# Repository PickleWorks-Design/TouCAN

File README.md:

# TouCAN

Personal Project To integrate 2 Can Adapters in 1 board with Deutch DT 3pin connectors and an onboard usb HUB

USB to Can Adapter

This Project is Based on the CANAble USB to Canbus adapter project https://github.com/makerbase-mks/CANable-MKS/tree/main/Hardware/MKS%20CANable%20V2.0

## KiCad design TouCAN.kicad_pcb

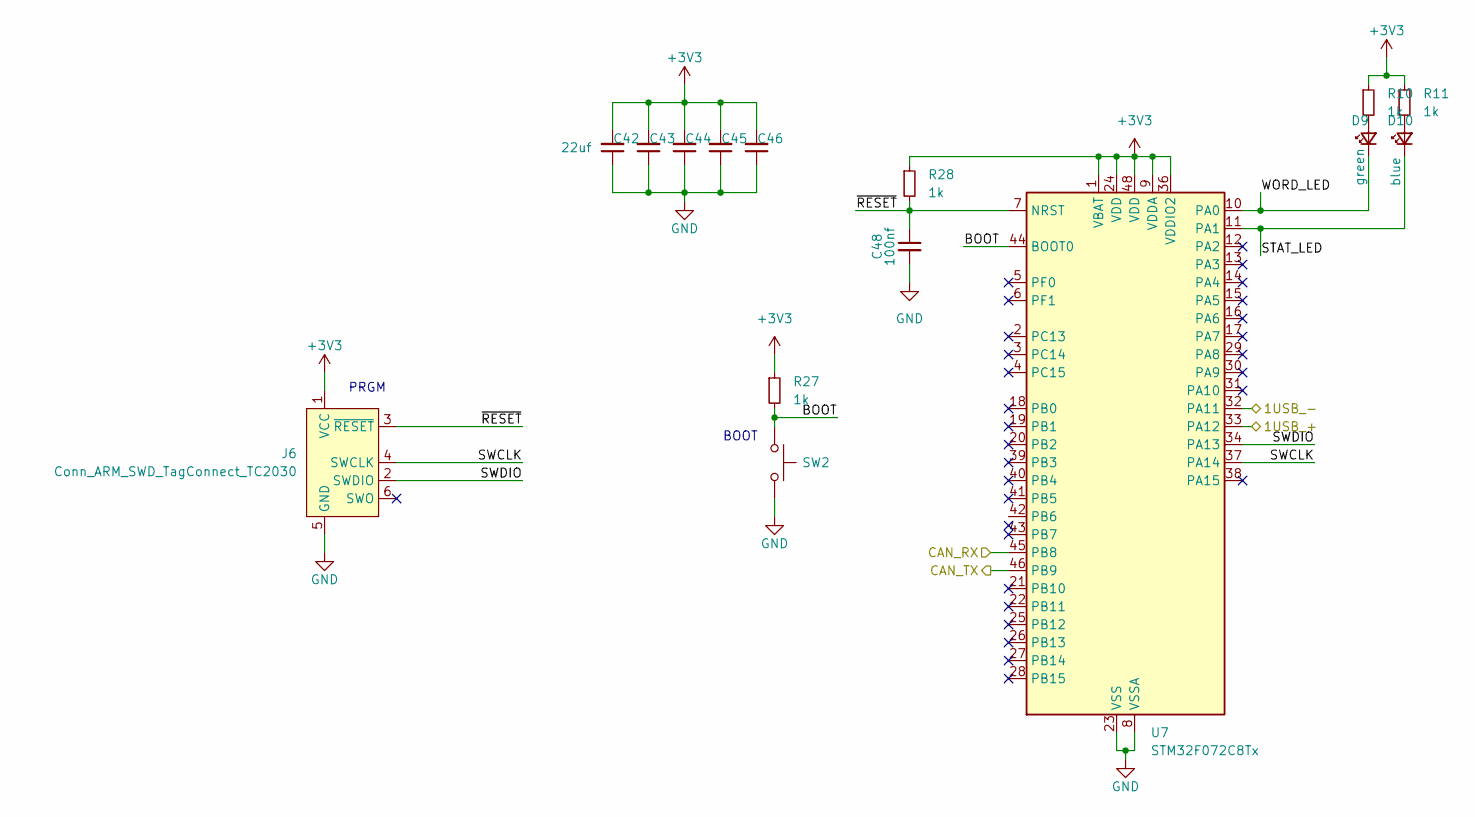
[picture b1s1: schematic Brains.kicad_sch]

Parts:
C42, C43, C44, C45, C46: 22uf; C_0603_1608Metric; LCSC C59461
C48: 100nf; C_0603_1608Metric; LCSC C14663
D9: green; LED_0603_1608Metric; LCSC C72043
D10: blue; LED_0603_1608Metric; LCSC C72041
J6: Conn_ARM_SWD_TagConnect_TC2030; Tag-Connect_TC2030-IDC-FP_2x03_P1.27mm_Vertical
R10, R11, R27, R28: 1k; R_0603_1608Metric; LCSC C21190
SW2: smol_button; LCSC C720477
U7: STM32F072C8Tx; LQFP-48_7x7mm_P0.5mm; LCSC C80488

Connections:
+3V3: C42.2, C43.2, C44.2, C45.2, C46.2, J6.1 (VCC), R10.1, R11.1, R27.1, R28.1, U7.1 (VBAT), U7.9 (VDDA), U7.24 (VDD), U7.36 (VDDIO2), U7.48 (VDD); also elsewhere on the board
/1USB_+: U7.33 (PA12); also elsewhere on the board
/1USB_-: U7.32 (PA11); also elsewhere on the board
/Brains/BOOT: R27.2, SW2.1, U7.44 (BOOT0)
/Brains/CAN_RX: U7.45 (PB8); also elsewhere on the board
/Brains/CAN_TX: U7.46 (PB9); also elsewhere on the board
/Brains/STAT_LED: D10.1 (K), U7.11 (PA1)
/Brains/SWCLK: J6.4 (SWCLK), U7.37 (PA14)
/Brains/SWDIO: J6.2 (SWDIO), U7.34 (PA13)
/Brains/WORD_LED: D9.1 (K), U7.10 (PA0)
/Brains/~RESET: C48.1, J6.3 (~RESET), R28.2, U7.7 (NRST)
GND: C42.1, C43.1, C44.1, C45.1, C46.1, C48.2, J6.5 (GND), SW2.2, U7.8 (VSSA), U7.23 (VSS), U7.35 (VSS), U7.47 (VSS); also elsewhere on the board
unnamed: D9.2 (A), R10.2
unnamed: D10.2 (A), R11.2

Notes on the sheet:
BOOT
PRGM

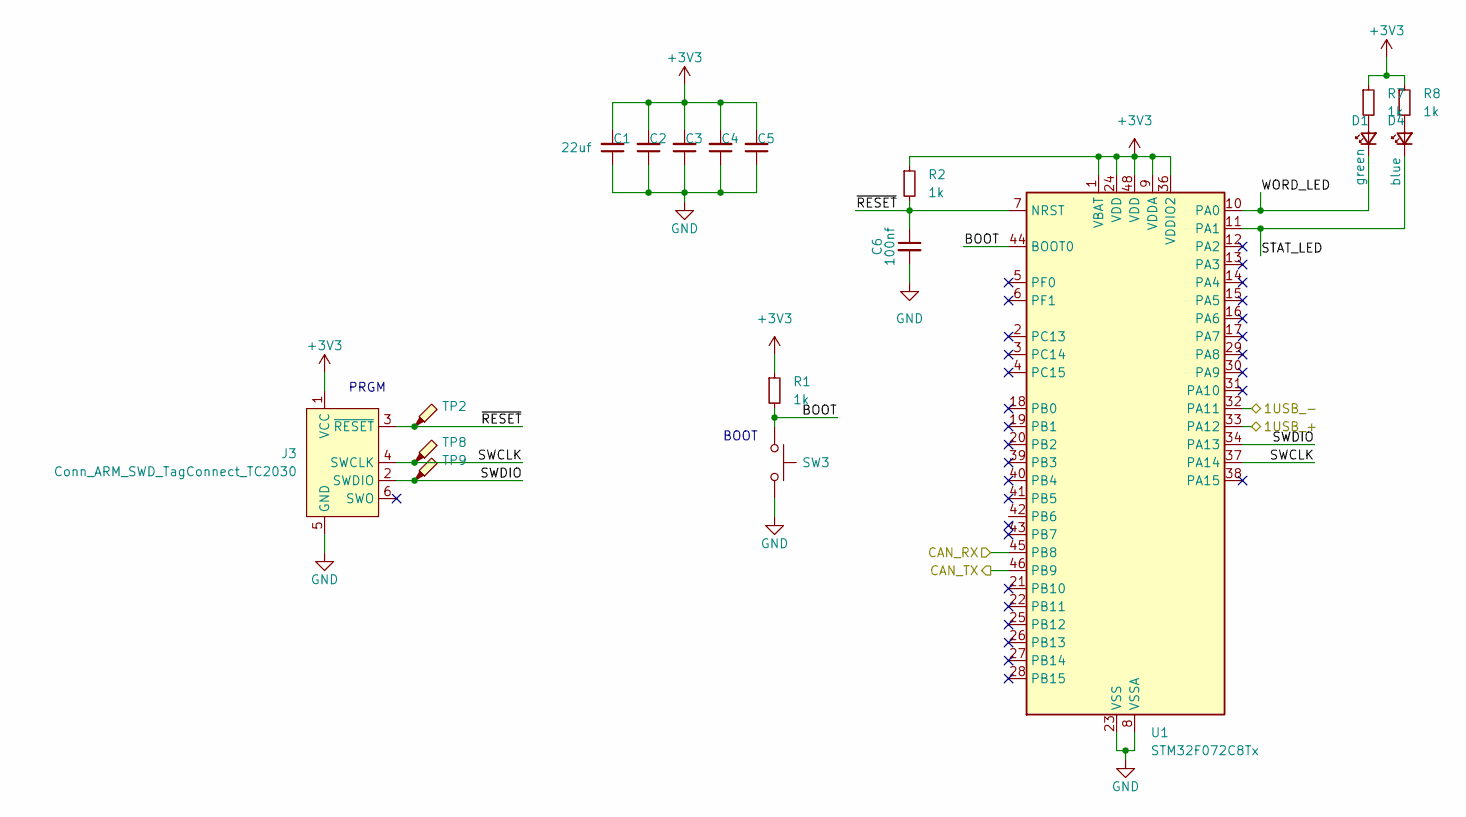
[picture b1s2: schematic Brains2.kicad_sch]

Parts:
C1, C2, C3, C4, C5: 22uf; C_0603_1608Metric; LCSC C59461
C6: 100nf; C_0603_1608Metric; LCSC C14663
D1: green; LED_0603_1608Metric; LCSC C72043
D4: blue; LED_0603_1608Metric; LCSC C72041
J3: Conn_ARM_SWD_TagConnect_TC2030; Tag-Connect_TC2030-IDC-FP_2x03_P1.27mm_Vertical
R1, R2, R7, R8: 1k; R_0603_1608Metric; LCSC C21190
SW3: smol_button; LCSC C720477
TP2, TP8, TP9: TestPoint_Probe
U1: STM32F072C8Tx; LQFP-48_7x7mm_P0.5mm; LCSC C80488

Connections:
+3V3: C1.2, C2.2, C3.2, C4.2, C5.2, J3.1 (VCC), R1.1, R2.1, R7.1, R8.1, U1.1 (VBAT), U1.9 (VDDA), U1.24 (VDD), U1.36 (VDDIO2), U1.48 (VDD); also elsewhere on the board
/2USB_+: U1.33 (PA12); also elsewhere on the board
/2USB_-: U1.32 (PA11); also elsewhere on the board
/Brains2/BOOT: R1.2, SW3.1, U1.44 (BOOT0)
/Brains2/CAN_RX: U1.45 (PB8); also elsewhere on the board
/Brains2/CAN_TX: U1.46 (PB9); also elsewhere on the board
/Brains2/STAT_LED: D4.1 (K), U1.11 (PA1)
/Brains2/SWCLK: J3.4 (SWCLK), TP8.1, U1.37 (PA14)
/Brains2/SWDIO: J3.2 (SWDIO), TP9.1, U1.34 (PA13)
/Brains2/WORD_LED: D1.1 (K), U1.10 (PA0)
/Brains2/~RESET: C6.1, J3.3 (~RESET), R2.2, TP2.1, U1.7 (NRST)
GND: C1.1, C2.1, C3.1, C4.1, C5.1, C6.2, J3.5 (GND), SW3.2, U1.8 (VSSA), U1.23 (VSS), U1.35 (VSS), U1.47 (VSS); also elsewhere on the board
unnamed: D1.2 (A), R7.2
unnamed: D4.2 (A), R8.2

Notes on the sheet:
BOOT
PRGM

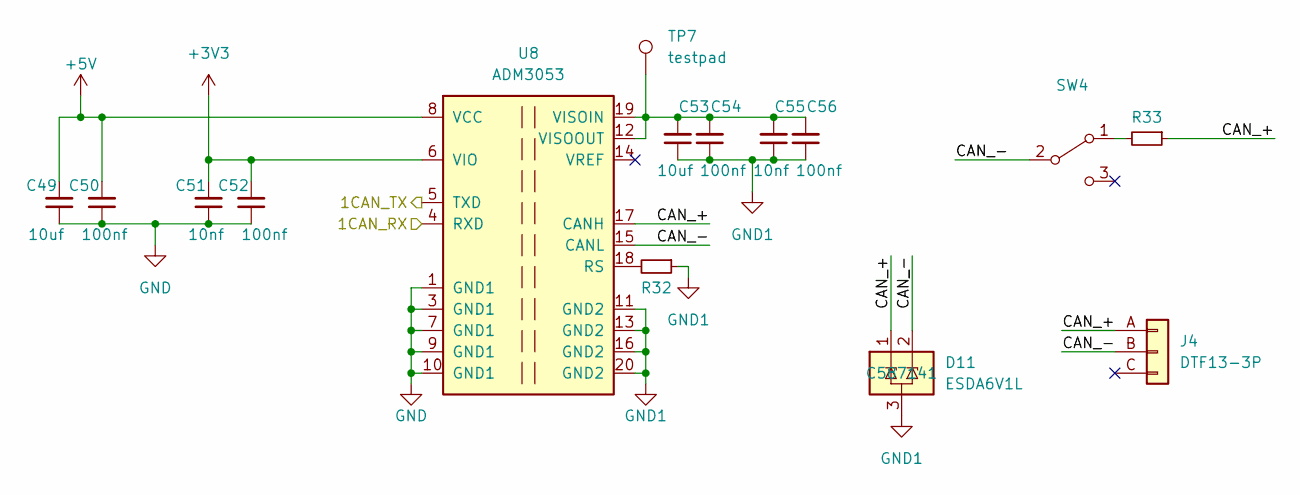
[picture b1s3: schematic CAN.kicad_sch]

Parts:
C49, C53: 10uf; C_0603_1608Metric; LCSC C96446
C50, C52, C54, C56: 100nf; C_0603_1608Metric; LCSC C14663
C51, C55: 10nf; C_0603_1608Metric; LCSC C57112
D11: ESDA6V1L; SOT-23-3; LCSC C587141
J4: DTF13-3P
R32: 10r; R_0603_1608Metric; LCSC C22859
R33: 120r; R_0603_1608Metric; LCSC C22787
SW4: MS-22C01-G010_pickle; LCSC C2837066
TP7: testpad; TestPoint_Pad_D1.0mm
U8: ADM3053; SOIC-20W_7.5x12.8mm_P1.27mm; LCSC C117821

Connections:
+3V3: C51.2, C52.2, U8.6 (VIO); also elsewhere on the board
+5V: C49.2, C50.2, U8.8 (VCC); also elsewhere on the board
/Brains/CAN_RX: U8.5 (TXD); also elsewhere on the board
/Brains/CAN_TX: U8.4 (RXD); also elsewhere on the board
/CAN/CAN_+: D11.1 (IO1), J4.A (Pin_1), R33.1, U8.17 (CANH)
/CAN/CAN_-: D11.2 (IO2), J4.B (Pin_2), SW4.2 (B), U8.15 (CANL)
GND: C49.1, C50.1, C51.1, C52.1, U8.1 (GND1), U8.3 (GND1), U8.7 (GND1), U8.9 (GND1), U8.10 (GND1); also elsewhere on the board
GND1: C53.1, C54.1, C55.1, C56.1, D11.3 (GND), R32.1, U8.11 (GND2), U8.13 (GND2), U8.16 (GND2), U8.20 (GND2)
unnamed: R33.2, SW4.1 (A)
unnamed: R32.2, U8.18 (RS)
unnamed: C53.2, C54.2, C55.2, C56.2, TP7.1, U8.12 (VISOOUT), U8.19 (VISOIN)

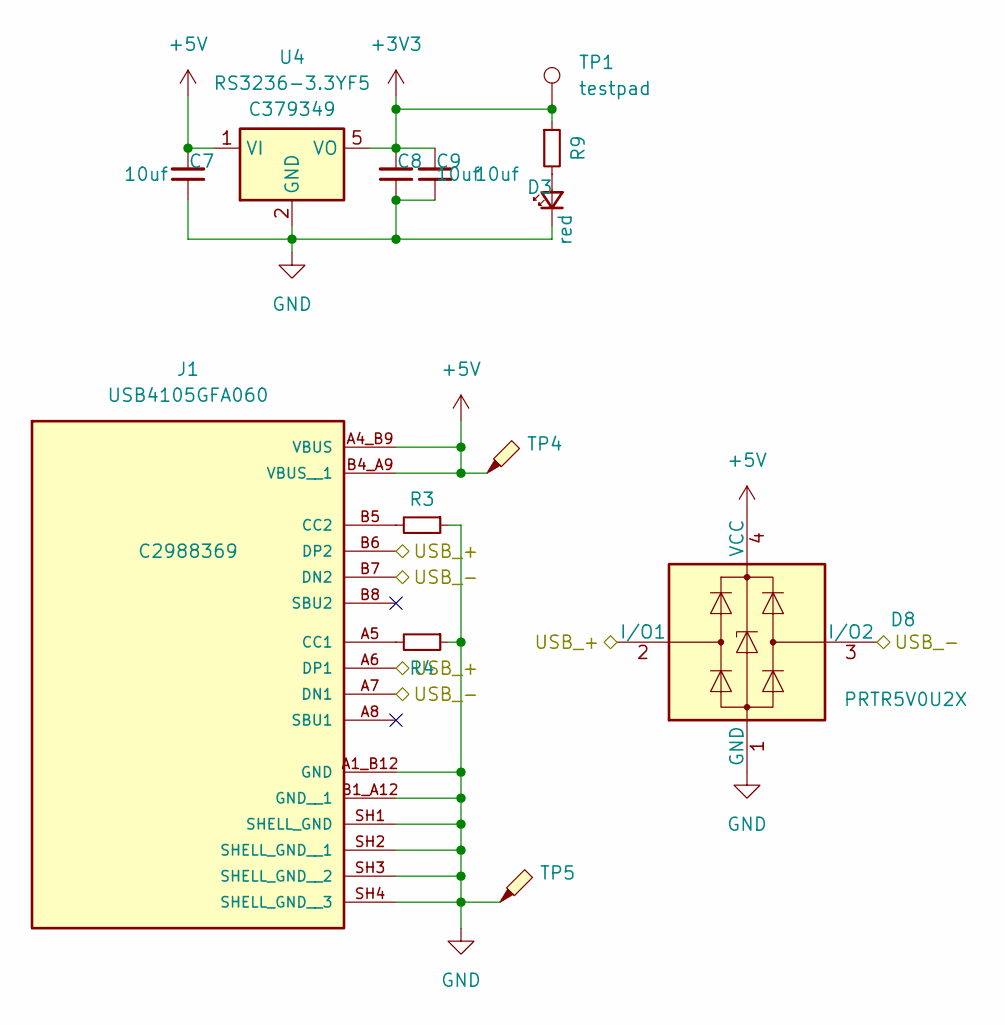
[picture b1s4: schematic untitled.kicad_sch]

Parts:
C7, C8, C9: 10uf; C_0603_1608Metric; LCSC C96446
D3: red; LED_0603_1608Metric; LCSC C72044
D8: PRTR5V0U2X; SOT-143; LCSC C2827688
J1: USB4105GFA060; USB_C_Receptacle_G-Switch_GT-USB-7010ASV_pickle; PARTREV B3; LCSC C2988369
R3, R4: 5.1k; R_0603_1608Metric; LCSC C23186
R9: 1k; R_0603_1608Metric; LCSC C21190
TP1: testpad; TestPoint_Pad_D1.0mm
TP4, TP5: TestPoint_Probe; TestPoint_Loop_D2.60mm_Drill1.4mm_Beaded
U4: RS3236-3.3YF5; SOT-23-5; LCSC C379349

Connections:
+3V3: C8.2, C9.2, R9.1, TP1.1, U4.5 (VO); also elsewhere on the board
+5V: C7.2, D8.4 (VCC), J1.A4_B9 (VBUS), J1.B4_A9 (VBUS__1), TP4.1, U4.1 (VI); also elsewhere on the board
/Power/USB_+: D8.2 (I/O1), J1.A6 (DP1), J1.B6 (DP2); also elsewhere on the board
/Power/USB_-: D8.3 (I/O2), J1.A7 (DN1), J1.B7 (DN2); also elsewhere on the board
GND: C7.1, C8.1, C9.1, D3.1 (K), D8.1 (GND), J1.A1_B12 (GND), J1.B1_A12 (GND__1), J1.SH1 (SHELL_GND), J1.SH2 (SHELL_GND__1), J1.SH3 (SHELL_GND__2), J1.SH4 (SHELL_GND__3), R3.1, R4.1, TP5.1, U4.2 (GND); also elsewhere on the board
unnamed: D3.2 (A), R9.2
unnamed: J1.A5 (CC1), R4.2
unnamed: J1.B5 (CC2), R3.2

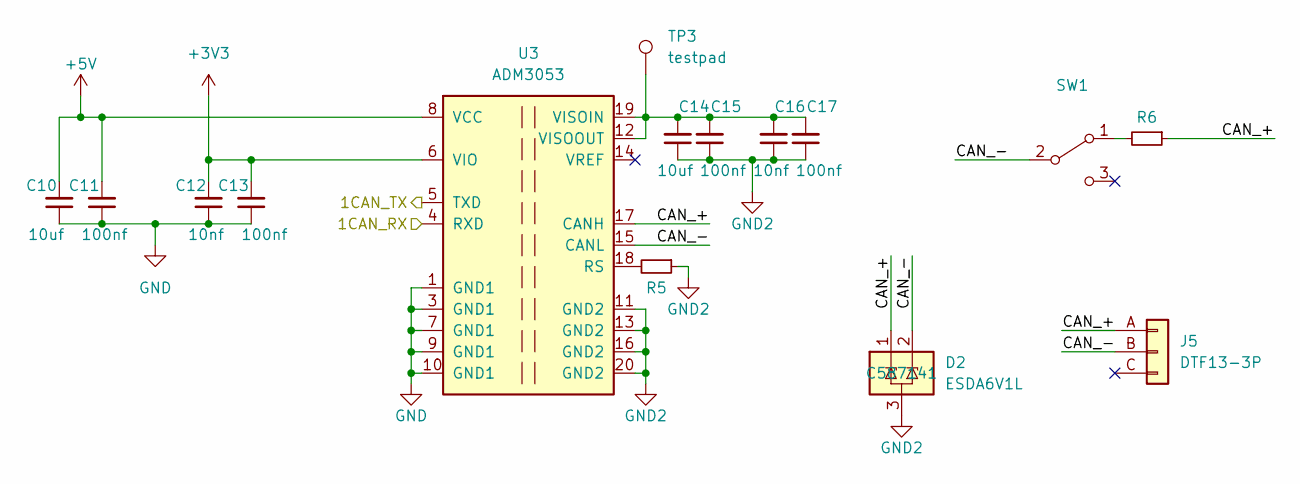
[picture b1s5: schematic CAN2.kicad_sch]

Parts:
C10, C14: 10uf; C_0603_1608Metric; LCSC C96446
C11, C13, C15, C17: 100nf; C_0603_1608Metric; LCSC C14663
C12, C16: 10nf; C_0603_1608Metric; LCSC C57112
D2: ESDA6V1L; SOT-23-3; LCSC C587141
J5: DTF13-3P
R5: 10r; R_0603_1608Metric; LCSC C22859
R6: 120r; R_0603_1608Metric; LCSC C22787
SW1: MS-22C01-G010_pickle; LCSC C2837066
TP3: testpad; TestPoint_Pad_D1.0mm
U3: ADM3053; SOIC-20W_7.5x12.8mm_P1.27mm; LCSC C117821

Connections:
+3V3: C12.2, C13.2, U3.6 (VIO); also elsewhere on the board
+5V: C10.2, C11.2, U3.8 (VCC); also elsewhere on the board
/Brains2/CAN_RX: U3.5 (TXD); also elsewhere on the board
/Brains2/CAN_TX: U3.4 (RXD); also elsewhere on the board
/CAN2/CAN_+: D2.1 (IO1), J5.A (Pin_1), R6.1, U3.17 (CANH)
/CAN2/CAN_-: D2.2 (IO2), J5.B (Pin_2), SW1.2 (B), U3.15 (CANL)
GND: C10.1, C11.1, C12.1, C13.1, U3.1 (GND1), U3.3 (GND1), U3.7 (GND1), U3.9 (GND1), U3.10 (GND1); also elsewhere on the board
GND2: C14.1, C15.1, C16.1, C17.1, D2.3 (GND), R5.1, U3.11 (GND2), U3.13 (GND2), U3.16 (GND2), U3.20 (GND2)
unnamed: R6.2, SW1.1 (A)
unnamed: R5.2, U3.18 (RS)
unnamed: C14.2, C15.2, C16.2, C17.2, TP3.1, U3.12 (VISOOUT), U3.19 (VISOIN)

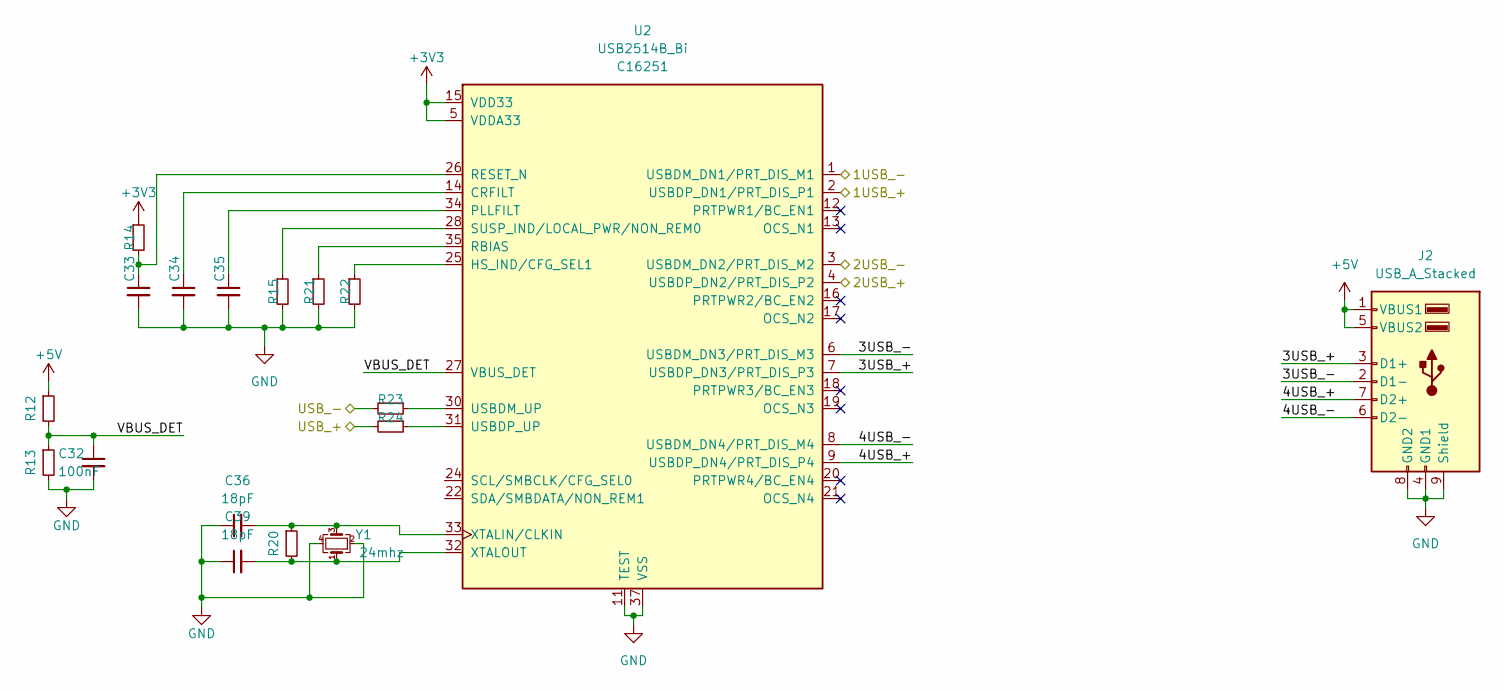
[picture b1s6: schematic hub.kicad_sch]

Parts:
C32, C33, C34, C35: 100nF; C_0402_1005Metric; LCSC C1525
C36, C39: 18pF; C_0402_1005Metric; LCSC C1549
J2: USB_A_Stacked; USB_A_CUI_UJ2-ADH-TH_Horizontal_Stacked; LCSC C456021
R12, R13, R14, R15, R22: 100k; R_0402_1005Metric; LCSC C25741
R20: 1M; R_0603_1608Metric; LCSC C3152128
R21: 12k; R_0402_1005Metric; LCSC C25752
R23, R24: 0R; R_0402_1005Metric; LCSC C25086
U2: USB2514B_Bi; QFN-36-1EP_6x6mm_P0.5mm_EP3.7x3.7mm; LCSC C16251
Y1: 24mhz; Crystal_SMD_3225-4Pin_3.2x2.5mm; LCSC C362370

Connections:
+3V3: R14.1, U2.5 (VDDA33), U2.10 (VDDA33), U2.15 (VDD33), U2.23 (VDD33), U2.29 (VDDA33), U2.36 (VDDA33); also elsewhere on the board
+5V: J2.1 (VBUS1), J2.5 (VBUS2), R12.1; also elsewhere on the board
/1USB_+: U2.2 (USBDP_DN1/PRT_DIS_P1); also elsewhere on the board
/1USB_-: U2.1 (USBDM_DN1/PRT_DIS_M1); also elsewhere on the board
/2USB_+: U2.4 (USBDP_DN2/PRT_DIS_P2); also elsewhere on the board
/2USB_-: U2.3 (USBDM_DN2/PRT_DIS_M2); also elsewhere on the board
/Power/USB_+: R24.2; also elsewhere on the board
/Power/USB_-: R23.2; also elsewhere on the board
/hub/3USB_+: J2.3 (D1+), U2.7 (USBDP_DN3/PRT_DIS_P3)
/hub/3USB_-: J2.2 (D1-), U2.6 (USBDM_DN3/PRT_DIS_M3)
/hub/4USB_+: J2.7 (D2+), U2.9 (USBDP_DN4/PRT_DIS_P4)
/hub/4USB_-: J2.6 (D2-), U2.8 (USBDM_DN4/PRT_DIS_M4)
/hub/VBUS_DET: C32.1, R12.2, R13.1, U2.27 (VBUS_DET)
GND: C32.2, C33.2, C34.2, C35.2, C36.1, C39.1, J2.4 (GND1), J2.8 (GND2), J2.9 (Shield), R13.2, R15.2, R21.2, R22.2, U2.11 (TEST), U2.37 (VSS), Y1.2, Y1.4; also elsewhere on the board
unnamed: C34.1, U2.14 (CRFILT)
unnamed: R22.1, U2.25 (HS_IND/CFG_SEL1)
unnamed: C35.1, U2.34 (PLLFILT)
unnamed: R21.1, U2.35 (RBIAS)
unnamed: C33.1, R14.2, U2.26 (RESET_N)
unnamed: R15.1, U2.28 (SUSP_IND/LOCAL_PWR/NON_REM0)
unnamed: R23.1, U2.30 (USBDM_UP)
unnamed: R24.1, U2.31 (USBDP_UP)
unnamed: C36.2, R20.1, U2.33 (XTALIN/CLKIN), Y1.3
unnamed: C39.2, R20.2, U2.32 (XTALOUT), Y1.1

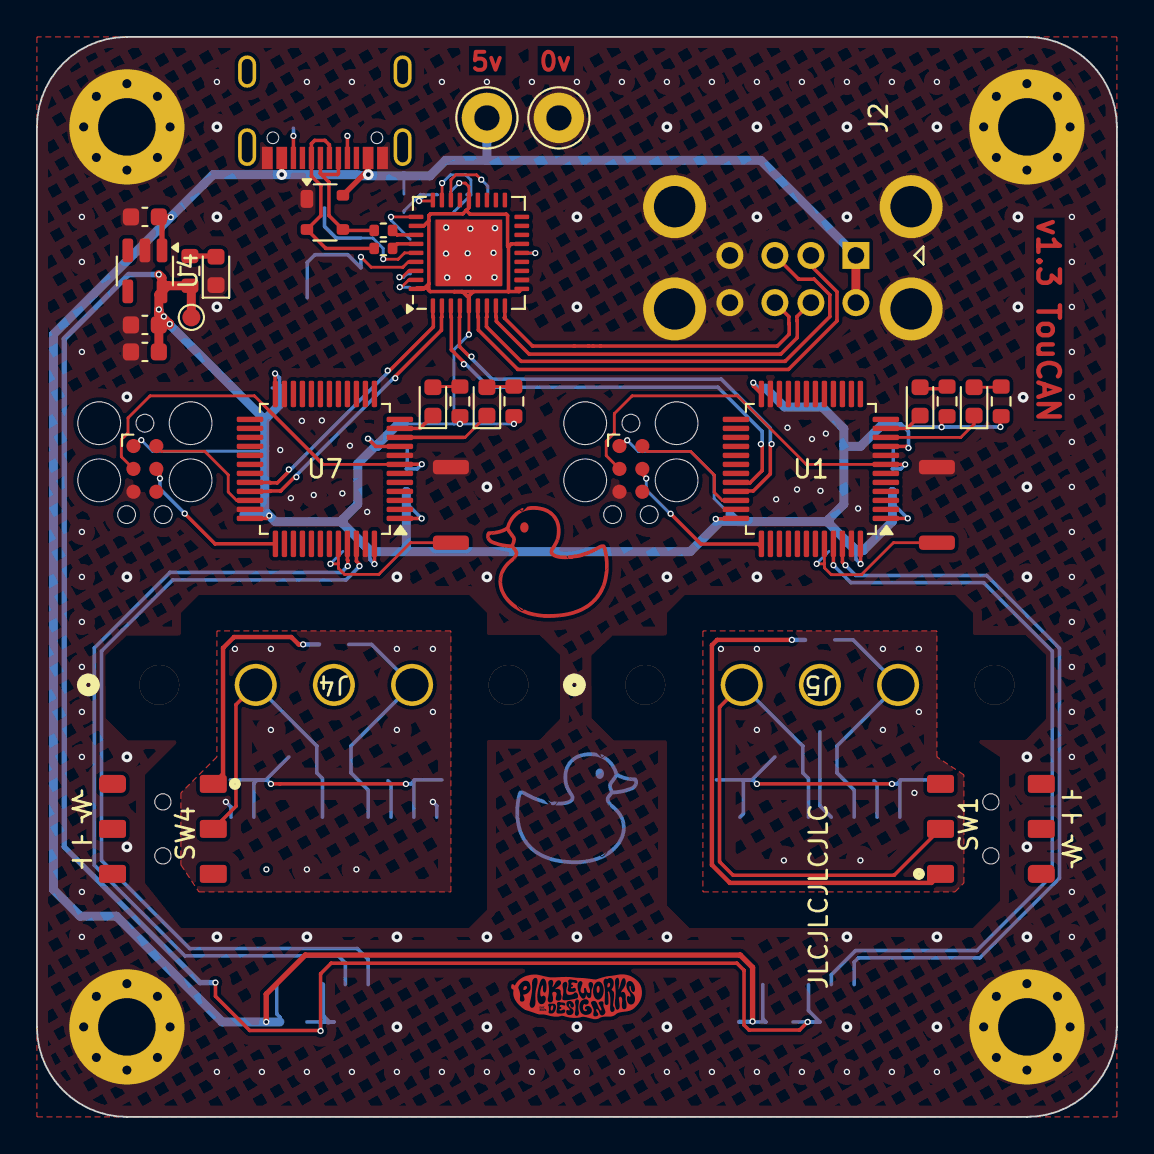
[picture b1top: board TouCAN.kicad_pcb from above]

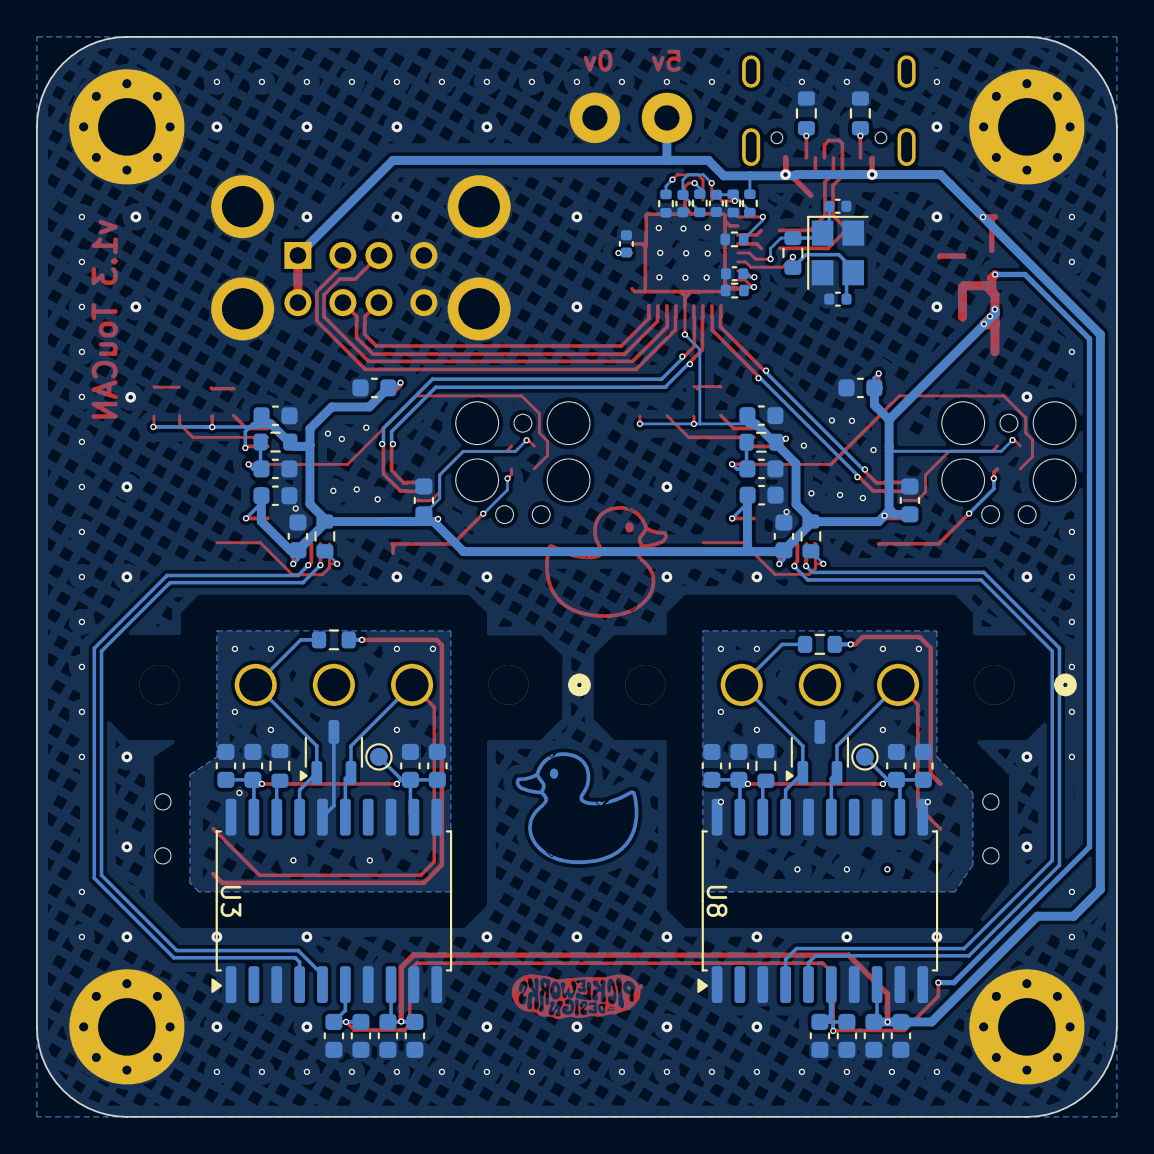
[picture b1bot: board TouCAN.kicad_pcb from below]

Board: 2 copper layers, 60.0 x 60.0 mm, 91 parts (58 on the bottom side), 59 nets.

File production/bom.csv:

Designator,Footprint,Quantity,Value,LCSC Part #
,af4c8d2e-6e3c-4016-b70e-df9501a44249,1,,
"C1, C2, C3, C4, C42, C43, C44, C45, C46, C5",0603,10,22uf,C59461
"C10, C14, C49, C53, C7, C8, C9",0603,7,10uf,C96446
"C11, C13, C15, C17, C48, C50, C52, C54, C56, C6",0603,10,100nf,C14663
"C12, C16, C51, C55",0603,4,10nf,C57112
"C32, C33, C34, C35",0402,4,100nF,C1525
"C36, C39",0402,2,18pF,C1549
"D1, D9",0603,2,green,C72043
"D10, D4",0603,2,blue,C72041
"D11, D2",SOT-23-3,2,ESDA6V1L,C587141
D3,0603,1,red,C72044
D8,SOT-143,1,PRTR5V0U2X,C2827688
J1,USB_C_Receptacle_G-Switch_GT-USB-7010ASV_pickle,1,USB4105GFA060,C2988369
J2,USB_A_CUI_UJ2-ADH-TH_Horizontal_Stacked,1,USB_A_Stacked,C456021
"J4, J5",DTF13-3P,2,DTF13-3P,
"R1, R10, R11, R2, R27, R28, R7, R8, R9",0603,9,1k,C21190
"R12, R13, R14, R15, R22",0402,5,100k,C25741
R20,0603,1,1M,C3152128
R21,0402,1,12k,C25752
"R23, R24",0402,2,0R,C25086
"R3, R4",0603,2,5.1k,C23186
"R32, R5",0603,2,10r,C22859
"R33, R6",0603,2,120r,C22787
"SW1, SW4",MS-22C01-G010_pickle,2,~,C2837066
"SW2, SW3",smol_button,2,smol_button,C720477
"TP1, TP3, TP7",TestPoint_Pad_D1.0mm,3,testpad,
"TP4, TP5",TestPoint_Loop_D2.60mm_Drill1.4mm_Beaded,2,TestPoint_Probe,
"U1, U7",LQFP-48_7x7mm_P0.5mm,2,STM32F072C8Tx,C80488
U2,QFN-36-1EP_6x6mm_P0.5mm_EP3.7x3.7mm,1,USB2514B_Bi,C16251
"U3, U8",SOIC-20W_7.5x12.8mm_P1.27mm,2,ADM3053,C117821
U4,SOT-23-5,1,RS3236-3.3YF5,C379349
Y1,Crystal_SMD_3225-4Pin_3.2x2.5mm,1,24mhz,C362370

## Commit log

2024-02-29 Uploaded Latest files
    Uploaded the latest design files
2024-02-29 added photo
2024-11-26 major changes removed m12 and changed layout
2024-11-26 added term switches
2024-12-10 added step
